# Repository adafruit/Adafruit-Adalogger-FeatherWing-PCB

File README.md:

## Adafruit FeatherWing - RTC + SD Add-on For All Feather Boards PCB

<a href="http://www.adafruit.com/products/2922"><br/>
Click here to purchase one from the Adafruit shop</a>

PCB files for the Adafruit FeatherWing - RTC + SD Add-on For All Feather Boards. Format is EagleCAD schematic and board layout
* https://www.adafruit.com/product/2922

### Description

A Feather board without ambition is a Feather board without FeatherWings! This is the **Adalogger FeatherWing**: it adds both a battery-backed Real Time Clock and micro SD card storage to any Feather main board. Using our [Feather Stacking Headers](https://www.adafruit.com/products/2830) or [Feather Female Headers](http://www.adafruit.com/products/2886) you can connect a FeatherWing on top of your Feather board and let the board take flight!

[Check out our range of Feather boards here.](https://www.adafruit.com/feather)

This FeatherWing will make it real easy to add datalogging to any of our existing Feathers. You get both an I2C real time clock (PCF8523) with 32KHz crystal and battery backup, and a microSD socket that connects to the SPI port pins (+ extra pin for CS). **Tested and works great with all of our Feathers.**

**Does not come with a micro SD card. A CR1220 coin cell is required to use the RTC battery-backup capabilities!** We don't include one by default, to make shipping easier for those abroad, [but we do stock them so pick one up or use any CR1220 you have handy](https://www.adafruit.com/products/380). If you're not using the RTC part of the FeatherWing, a battery is not required.[If you need a precision RTC, check out our DS3231 FeatherWing](https://www.adafruit.com/products/3028)

For pinouts, wiring and code example that will run on all Feathers, [check out the tutorial guide which we keep updated as new Feathers come out. It has more information including diagrams, example code for both Arduino and CircuitPython, pinouts, and more!](http://learn.adafruit.com/adafruit-adalogger-featherwing)

### License

Adafruit invests time and resources providing this open source design, please support Adafruit and open-source hardware by purchasing products from [Adafruit](https://www.adafruit.com)!

Designed by Limor Fried/Ladyada for Adafruit Industries.

Creative Commons Attribution/Share-Alike, all text above must be included in any redistribution. See license.txt for additional details.

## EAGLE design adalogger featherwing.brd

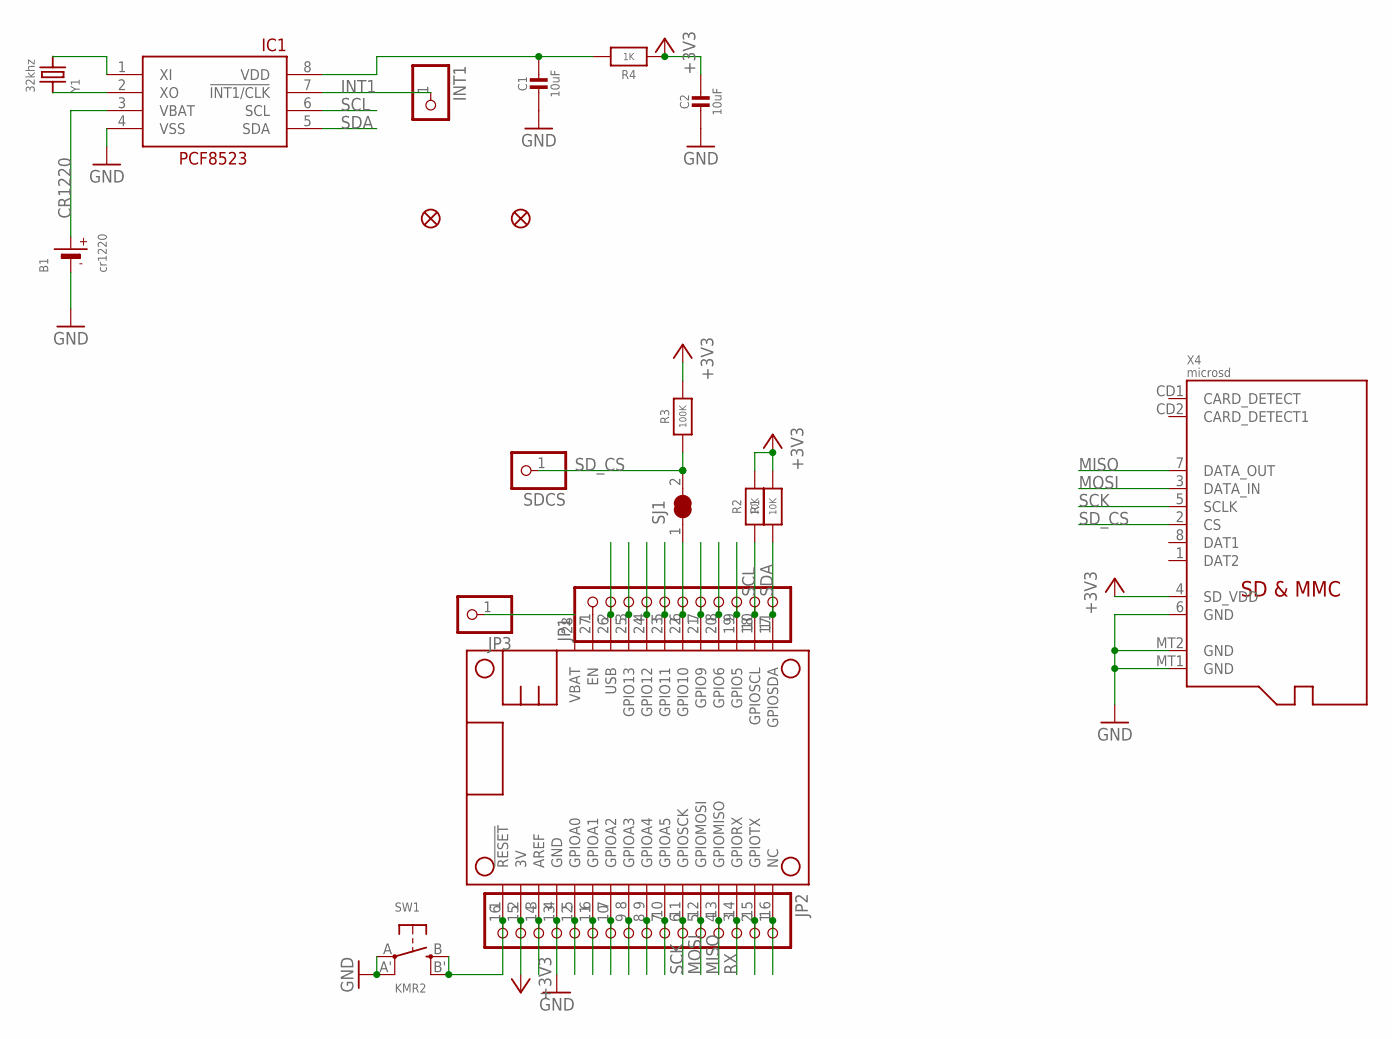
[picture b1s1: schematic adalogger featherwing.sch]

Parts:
B1: cr1220; CR1220-2
C1, C2: 10uF; 0805-NO
FID1, FID2: FIDUCIAL_1MM
IC1: PCF8523T; SOIC8_150MIL
INT1: HEADER-1X1ROUND; 1X01_ROUND
JP1: HEADER-1X11; 1X11_ROUND
JP2: HEADER-1X16ROUND; 1X16_ROUND
JP3: HEADER-1X1ROUND; 1X01_ROUND
MS1: FEATHERWING_NODIM
R1, R2: 10K; 0603-NO
R3: 100K; 0603-NO
R4: 1K; 0603-NO
SDCS: HEADER-1X1ROUND; 1X01_ROUND
SJ1: SOLDERJUMPER_CLOSED; SOLDERJUMPER_CLOSEDWIRE
SW1: KMR2; BTN_KMR2_4.6X2.8
X4: microsd; MICROSD
Y1: 32khz; CRYSTAL_8X3.8

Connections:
+3V3: C2.1, JP2.15, MS1.2 (3V), R1.2, R2.2, R3.2, R4.1, X4.4 (SD_VDD)
A: JP2.12, MS1.5 (GPIOA0)
AREF: JP2.14, MS1.3 (AREF)
B: JP2.11, MS1.6 (GPIOA1)
C: JP2.10, MS1.7 (GPIOA2)
CR1220: B1.+, IC1.3 (VBAT)
CS: JP1.6, MS1.22 (GPIO10), SJ1.1
D: JP2.9, MS1.8 (GPIOA3)
E: JP2.8, MS1.9 (GPIOA4)
EN: JP1.1, MS1.27 (EN)
F: JP2.7, MS1.10 (GPIOA5)
G: JP2.1, MS1.16 (NC)
GND: B1.-, C1.2, C2.2, IC1.4 (VSS), JP2.13, MS1.4 (GND), SW1.A, SW1.A' (P1), X4.6 (GND), X4.MT1 (GND), X4.MT2 (GND)
H: JP1.9, MS1.19 (GPIO5)
I: JP1.8, MS1.20 (GPIO6)
INT1: IC1.7 (!INT1/CLK), INT1.1
J: JP1.7, MS1.21 (GPIO9)
L: JP1.5, MS1.23 (GPIO11)
M: JP1.4, MS1.24 (GPIO12)
MISO: JP2.4, MS1.13 (GPIOMISO), X4.7 (DATA_OUT)
MOSI: JP2.5, MS1.12 (GPIOMOSI), X4.3 (DATA_IN)
N: JP1.3, MS1.25 (GPIO13)
unnamed: C1.1, IC1.8 (VDD), R4.2
unnamed: IC1.1 (XI), Y1.P$4 (2)
unnamed: IC1.2 (XO), Y1.P$1 (1)
RESET: JP2.16, MS1.1 (!RESET), SW1.B (S), SW1.B' (S1)
RX: JP2.3, MS1.14 (GPIORX)
SCK: JP2.6, MS1.11 (GPIOSCK), X4.5 (SCLK)
SCL: IC1.6 (SCL), JP1.10, MS1.18 (GPIOSCL), R2.1
SDA: IC1.5 (SDA), JP1.11, MS1.17 (GPIOSDA), R1.1
SD_CS: R3.1, SDCS.1, SJ1.2, X4.2 (CS)
TX: JP2.2, MS1.15 (GPIOTX)
USB: JP1.2, MS1.26 (USB)
VBAT: JP3.1, MS1.28 (VBAT)

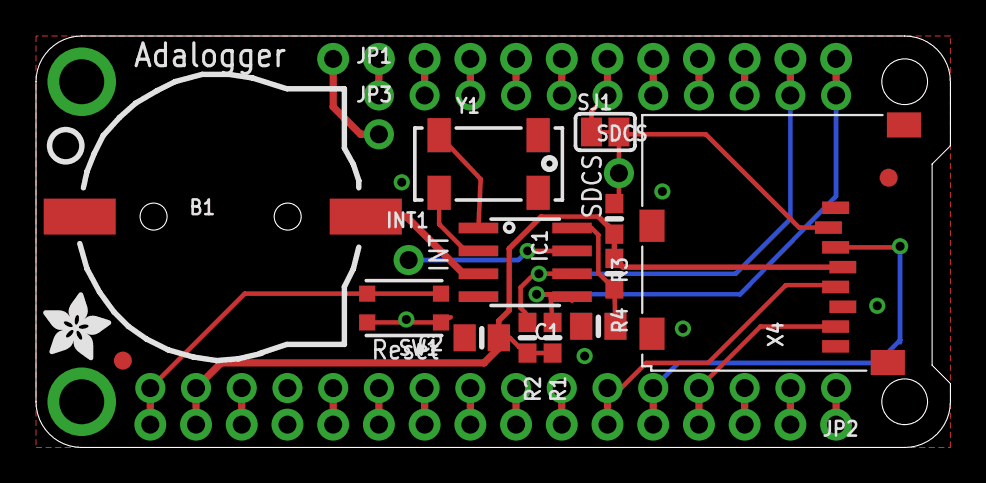
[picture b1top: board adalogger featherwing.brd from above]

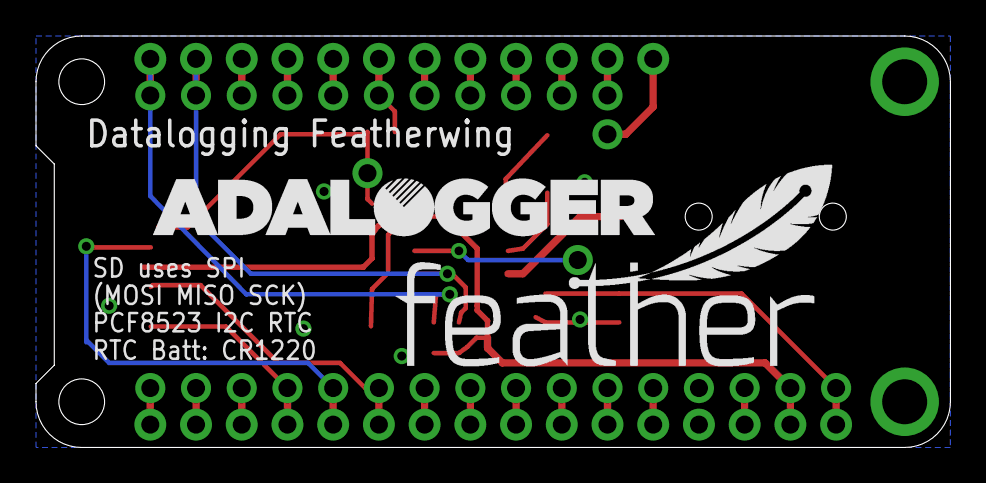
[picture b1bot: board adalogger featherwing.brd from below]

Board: 2 copper layers, 50.8 x 22.9 mm, 24 parts (2 on the bottom side), 34 nets.

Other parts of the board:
U$2: FEATHERLOGO
U$3: ADALOGGER_LOGO
U$4: ADAFRUIT_3.5MM
U$5: PCBFEAT-REV-040

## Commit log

2016-05-09 files!
2016-05-09 reaaaad me
2017-07-21 update with RC filter
2018-11-23 Create v2
2018-11-23 schematic update
    Update the schematic because is better.
2019-07-16 updated to use cookiecutter for pcb repos
